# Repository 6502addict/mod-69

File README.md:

# MOD-69

<br>

## Description
This module permit to connect a 6809 or a 6809E processor
into a 6502 socket.
<br>
This type of product existed ont the Synertek SYM-1

## Note:
this development is just for fun there is no warranty of any kind
that this mod-69 will work on your machine...
please report the success / failure...
I'll try to improved the mod-69 and support new machines
as well as the 6809 monitor code

## ChangeLog:

1.2  Rework of the silk mask
     2 10k pull up added on IRQ and FIRQ lines

1.1  oscillator replace by a frequency multiplier
     connected to phi0
     dip switch replaced by jumpers
     
1.0  initial version using a 50Mhz oscillator

## JUMPERS
```
OP1     reserved for futur function
OP0     reserved for futur function
SAL     select 65XX socket type
           jumper removed: standard 6502
           jumper set:     6502C (SALLY)
69E     select 6809/6809E processor type
           jumper removed: 6809  (no support for sync) 
           jumper set:     6809E (support for sync)
IRQ     place a jumper on IRQ to map 6502 IRQ to 6809 IRQ       
FIRQ    place a jumper on FIRQ to map 6502 IRQ to 6809 FIRQ
U1      DO NOT USE... (for debug)
U0      DO NOT USE... (for debug)
```

## Note
* Even if SALLY it was planned, it is not yet supported

## PCB
the pcb can be ordered from oshpark<br>
https://oshpark.com/shared_projects/tMBBF8oK

## Bill of Materials
* 1 PLCC 44 socket
* 1 DIP 40 socket 600mil
* 1 Pin Header Strip 1 Row Machined 40Pin Male Round
    break the strip in 2 x 20 pin 
* 1 EPM7064S
* 1 NB3N502DG
* 4 resistors  3.3k  1206
* 2 resistors   10k  1206
* 6 capacitors 100nf 1206
* 1 2.54mm 2x5 male pin header
* 1 2.54mm 2x8 male pin header
* 2 jumpers

## Build of the board
the easiest is to solder the component in the following order<br>
1. NB3N502DG<br>
2. 6 x 100nf capacitors<br>
3. 2 x 10k resistors<br>
4. 4 x 3.3k resistors<br>
5. 2 x 20 pin strips<br>
   install the strips before the 40 pin DIP socket !!!<br>
   use a breadboard or another socket to align correctly the pins<br>
6. PLCC4 sockets<br
7. DIP 40 socket<br>
8. 2.54mm 2x5 male pin header (jtag)
9. 2.54mm 2x8 male pin header (options)
10. insert a jumper on IRQ or FIRQ
11. insert a jumper on 69E if you want to use a 6809E

## CPLD Progamming
The programming files are in vhdl directory<br>
you need Quartus II 13.0sp1 to modify this project<br>
the CPLD type is an EPM7064S PLCC 44<br>
<br>
To import this project in Quartus<br>
create a new project name "mod-69"<br>
and insert the files from github<br>
the top level is "mod69.vhd"<br>
<br>
if you only want to program the CPLD<br>
connect the adapter to a USB Blaster with a flat
cable then use the mod69.pof.<br>

# Futur Enhancement...
Only a half of cpld capacity is used so there is
enough room to support sally or solve conflit 
on some specific machines...

the jumper OP1 et OP2 are there to solve 
specific cases

# Machines tested

## SYNERTEK SYM-1
the SYM-1 worked fine with my first version of MOD-69
but the way the clock is generated on the SYM-1 makes it incompatible with my second MOD-69
I'm preparing a third version to fix the probleme

## REPLICA 1
Works fine with my second version of MOD-69 either with a 6809 or a 6809E as well as with 6309/6309E

<br>
REPLICA 1 with MOD-69 plugged in place of the 6502
<br>
<br>

<br>
REPLICA 1 Running the 6809 monitor
<br>

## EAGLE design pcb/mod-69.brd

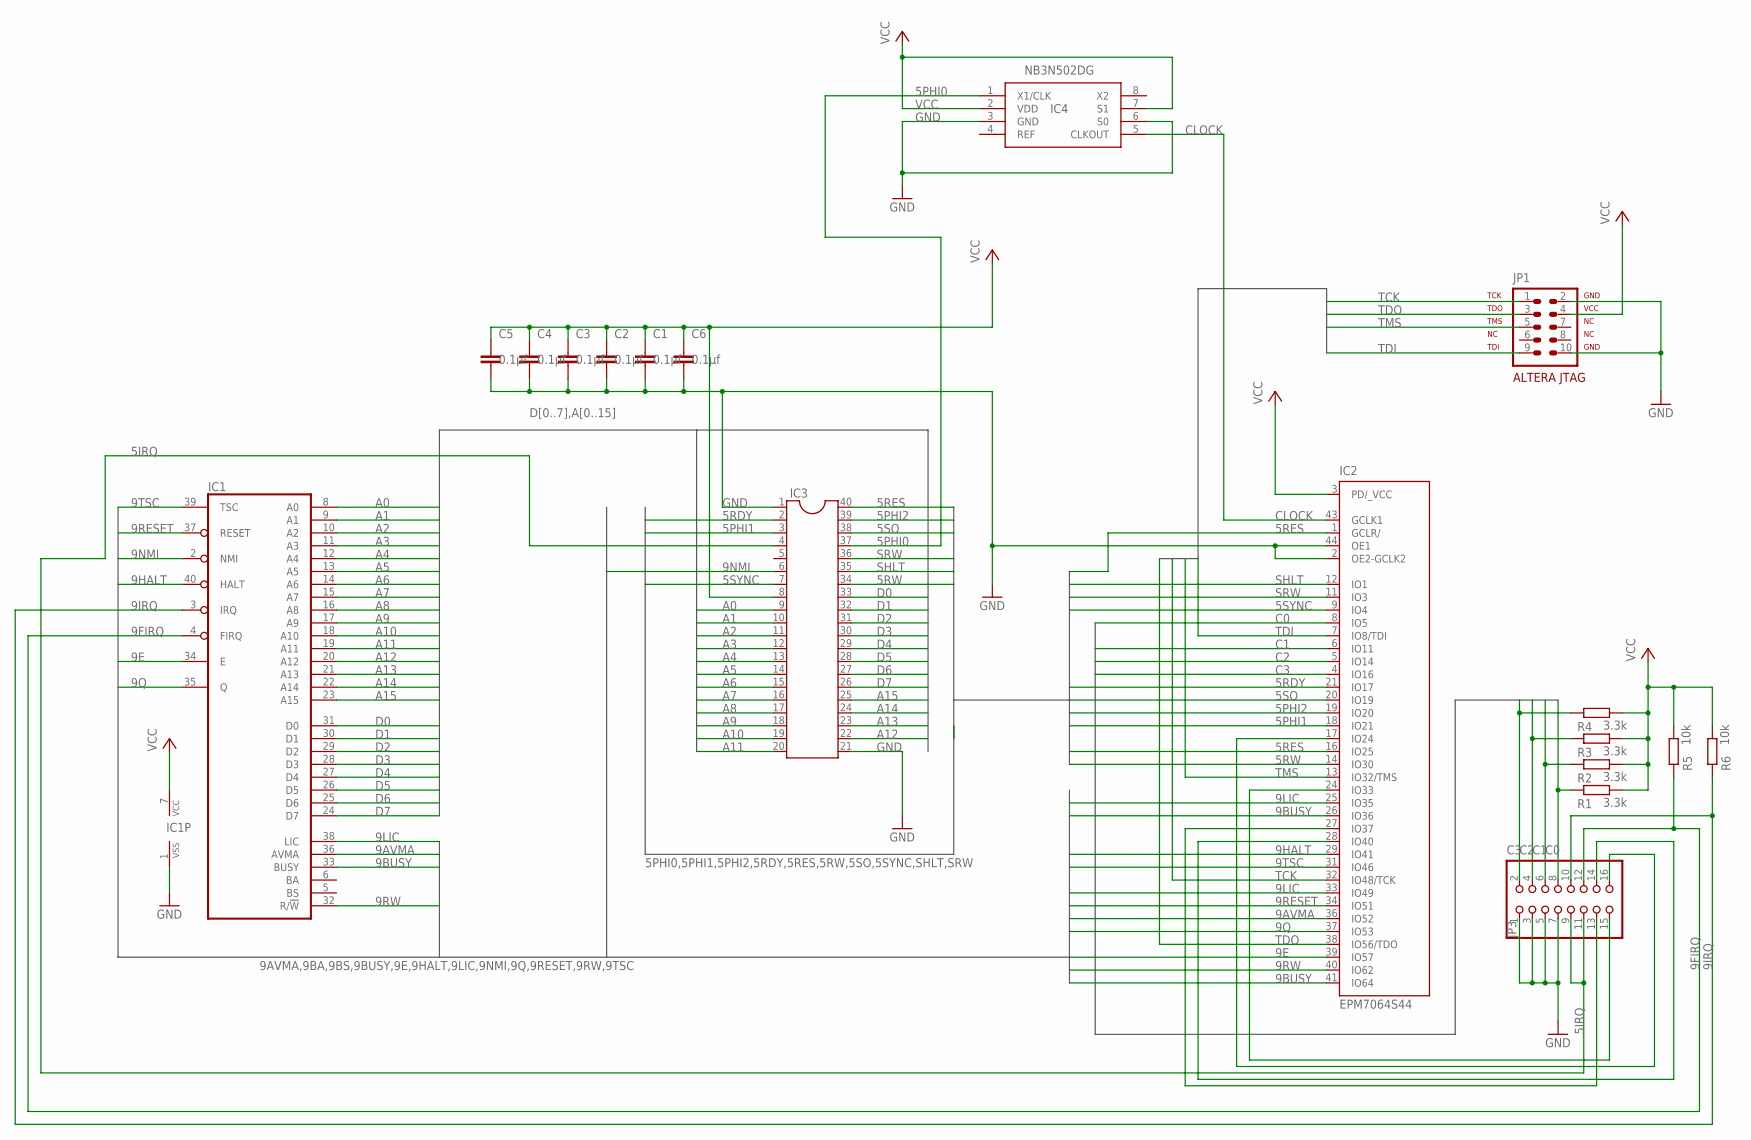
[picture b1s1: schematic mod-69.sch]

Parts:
C1, C2, C3, C4, C5, C6: 0.1µf; C1206
IC1: 6809E; DIL40
IC2: EPM7064S44; PLCC-S44
IC3: DIL40
IC4: NB3N502DG; SOIC127P600X175-8N
JP1: ALTERA-JTAG-10
JP3: PINHD-2X8; 2X08
R1, R2, R3, R4: 3.3k; M1206
R5, R6: 10k; M1206

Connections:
5IRQ: IC3.4, JP3.9, JP3.11
5PHI0: IC3.37, IC4.1 (X1/CLK)
5PHI1: IC2.18 (IO21), IC3.3
5PHI2: IC2.19 (IO20), IC3.39
5RDY: IC2.21 (IO17), IC3.2
5RES: IC2.1 (GCLR/), IC2.16 (IO25), IC3.40
5RW: IC2.14 (IO30), IC3.34
5SO: IC2.20 (IO19), IC3.38
5SYNC: IC2.9 (IO4), IC3.7
9AVMA: IC1.36 (AVMA), IC2.36 (IO52)
9BUSY: IC1.33 (BUSY), IC2.26 (IO36), IC2.41 (IO64)
9E: IC1.34 (E), IC2.39 (IO57)
9FIRQ: IC1.4 (FIRQ), JP3.12, R5.1
9HALT: IC1.40 (HALT), IC2.29 (IO41)
9IRQ: IC1.3 (IRQ), JP3.10, R6.1
9LIC: IC1.38 (LIC), IC2.25 (IO35), IC2.33 (IO49)
9NMI: IC1.2 (NMI), IC3.6
9Q: IC1.35 (Q), IC2.37 (IO53)
9RESET: IC1.37 (RESET), IC2.34 (IO51)
9RW: IC1.32 (R/!W), IC2.40 (IO62)
9TSC: IC1.39 (TSC), IC2.31 (IO46)
A0: IC1.8 (A0), IC3.9
A1: IC1.9 (A1), IC3.10
A2: IC1.10 (A2), IC3.11
A3: IC1.11 (A3), IC3.12
A4: IC1.12 (A4), IC3.13
A5: IC1.13 (A5), IC3.14
A6: IC1.14 (A6), IC3.15
A7: IC1.15 (A7), IC3.16
A8: IC1.16 (A8), IC3.17
A9: IC1.17 (A9), IC3.18
A10: IC1.18 (A10), IC3.19
A11: IC1.19 (A11), IC3.20
A12: IC1.20 (A12), IC3.22
A13: IC1.21 (A13), IC3.23
A14: IC1.22 (A14), IC3.24
A15: IC1.23 (A15), IC3.25
C0: IC2.8 (IO5), JP3.8, R1.1
C1: IC2.6 (IO11), JP3.6, R2.1
C2: IC2.5 (IO14), JP3.4, R3.1
C3: IC2.4 (IO16), JP3.2, R4.1
CLOCK: IC2.43 (GCLK1), IC4.5 (CLKOUT)
D0: IC1.31 (D0), IC3.33
D1: IC1.30 (D1), IC3.32
D2: IC1.29 (D2), IC3.31
D3: IC1.28 (D3), IC3.30
D4: IC1.27 (D4), IC3.29
D5: IC1.26 (D5), IC3.28
D6: IC1.25 (D6), IC3.27
D7: IC1.24 (D7), IC3.26
GND: C1.2, C2.2, C3.2, C4.2, C5.2, C6.2, IC1.1 (VSS), IC2.2 (OE2-GCLK2), IC2.10 (GND), IC2.22 (GND), IC2.30 (GND), IC2.42 (GND), IC2.44 (OE1), IC3.1, IC3.21, IC4.3 (GND), IC4.6 (S0), JP1.2 (GND1), JP1.10 (GND2), JP3.1, JP3.3, JP3.5, JP3.7
unnamed: IC2.27 (IO37), JP3.13
unnamed: IC2.28 (IO40), JP3.14
unnamed: IC2.24 (IO33), JP3.15
unnamed: IC2.17 (IO24), JP3.16
SHLT: IC2.12 (IO1), IC3.35
SRW: IC2.11 (IO3), IC3.36
TCK: IC2.32 (IO48/TCK), JP1.1 (TCK)
TDI: IC2.7 (IO8/TDI), JP1.9 (TDI)
TDO: IC2.38 (IO56/TDO), JP1.3 (TDO)
TMS: IC2.13 (IO32/TMS), JP1.5 (TMS)
VCC: C1.1, C2.1, C3.1, C4.1, C5.1, C6.1, IC1.7 (VCC), IC2.3 (PD/_VCC), IC2.15 (VCC), IC2.23 (VCC), IC2.35 (VCC), IC3.8, IC4.2 (VDD), IC4.7 (S1), JP1.4 (VCC), R1.2, R2.2, R3.2, R4.2, R5.2, R6.2

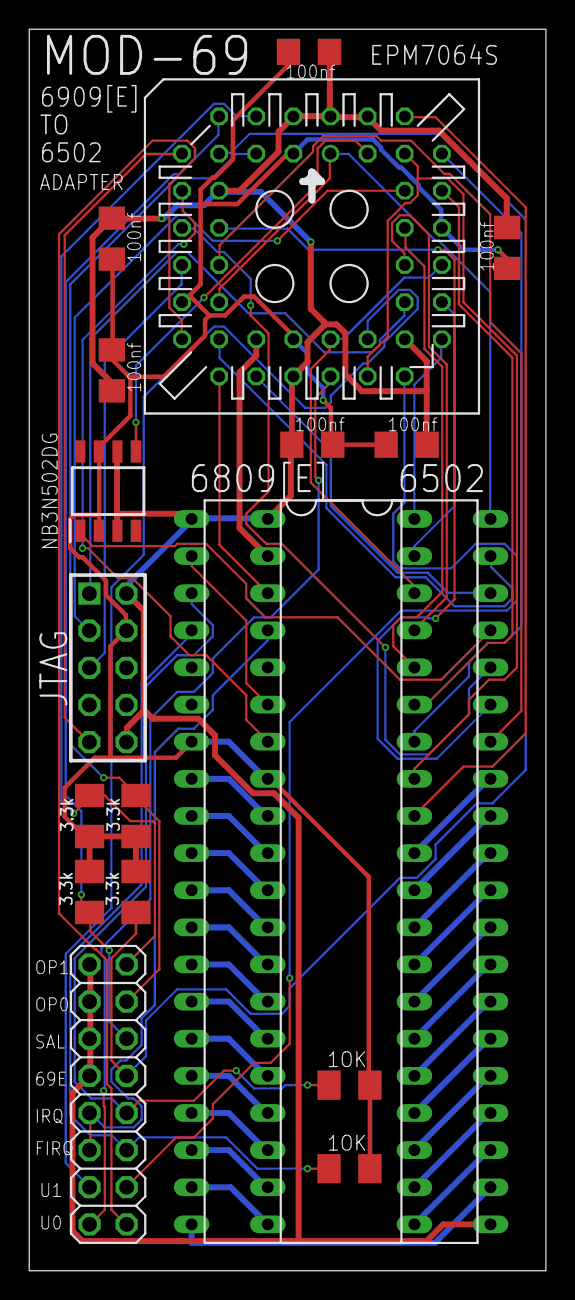
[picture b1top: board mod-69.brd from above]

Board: 2 copper layers, 35.3 x 84.9 mm, 18 parts (0 on the bottom side), 62 nets.

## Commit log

2021-02-07 Create x
2021-02-08 Create vhdl
2021-02-08 Create xxxx
2021-02-08 Update xxxx
